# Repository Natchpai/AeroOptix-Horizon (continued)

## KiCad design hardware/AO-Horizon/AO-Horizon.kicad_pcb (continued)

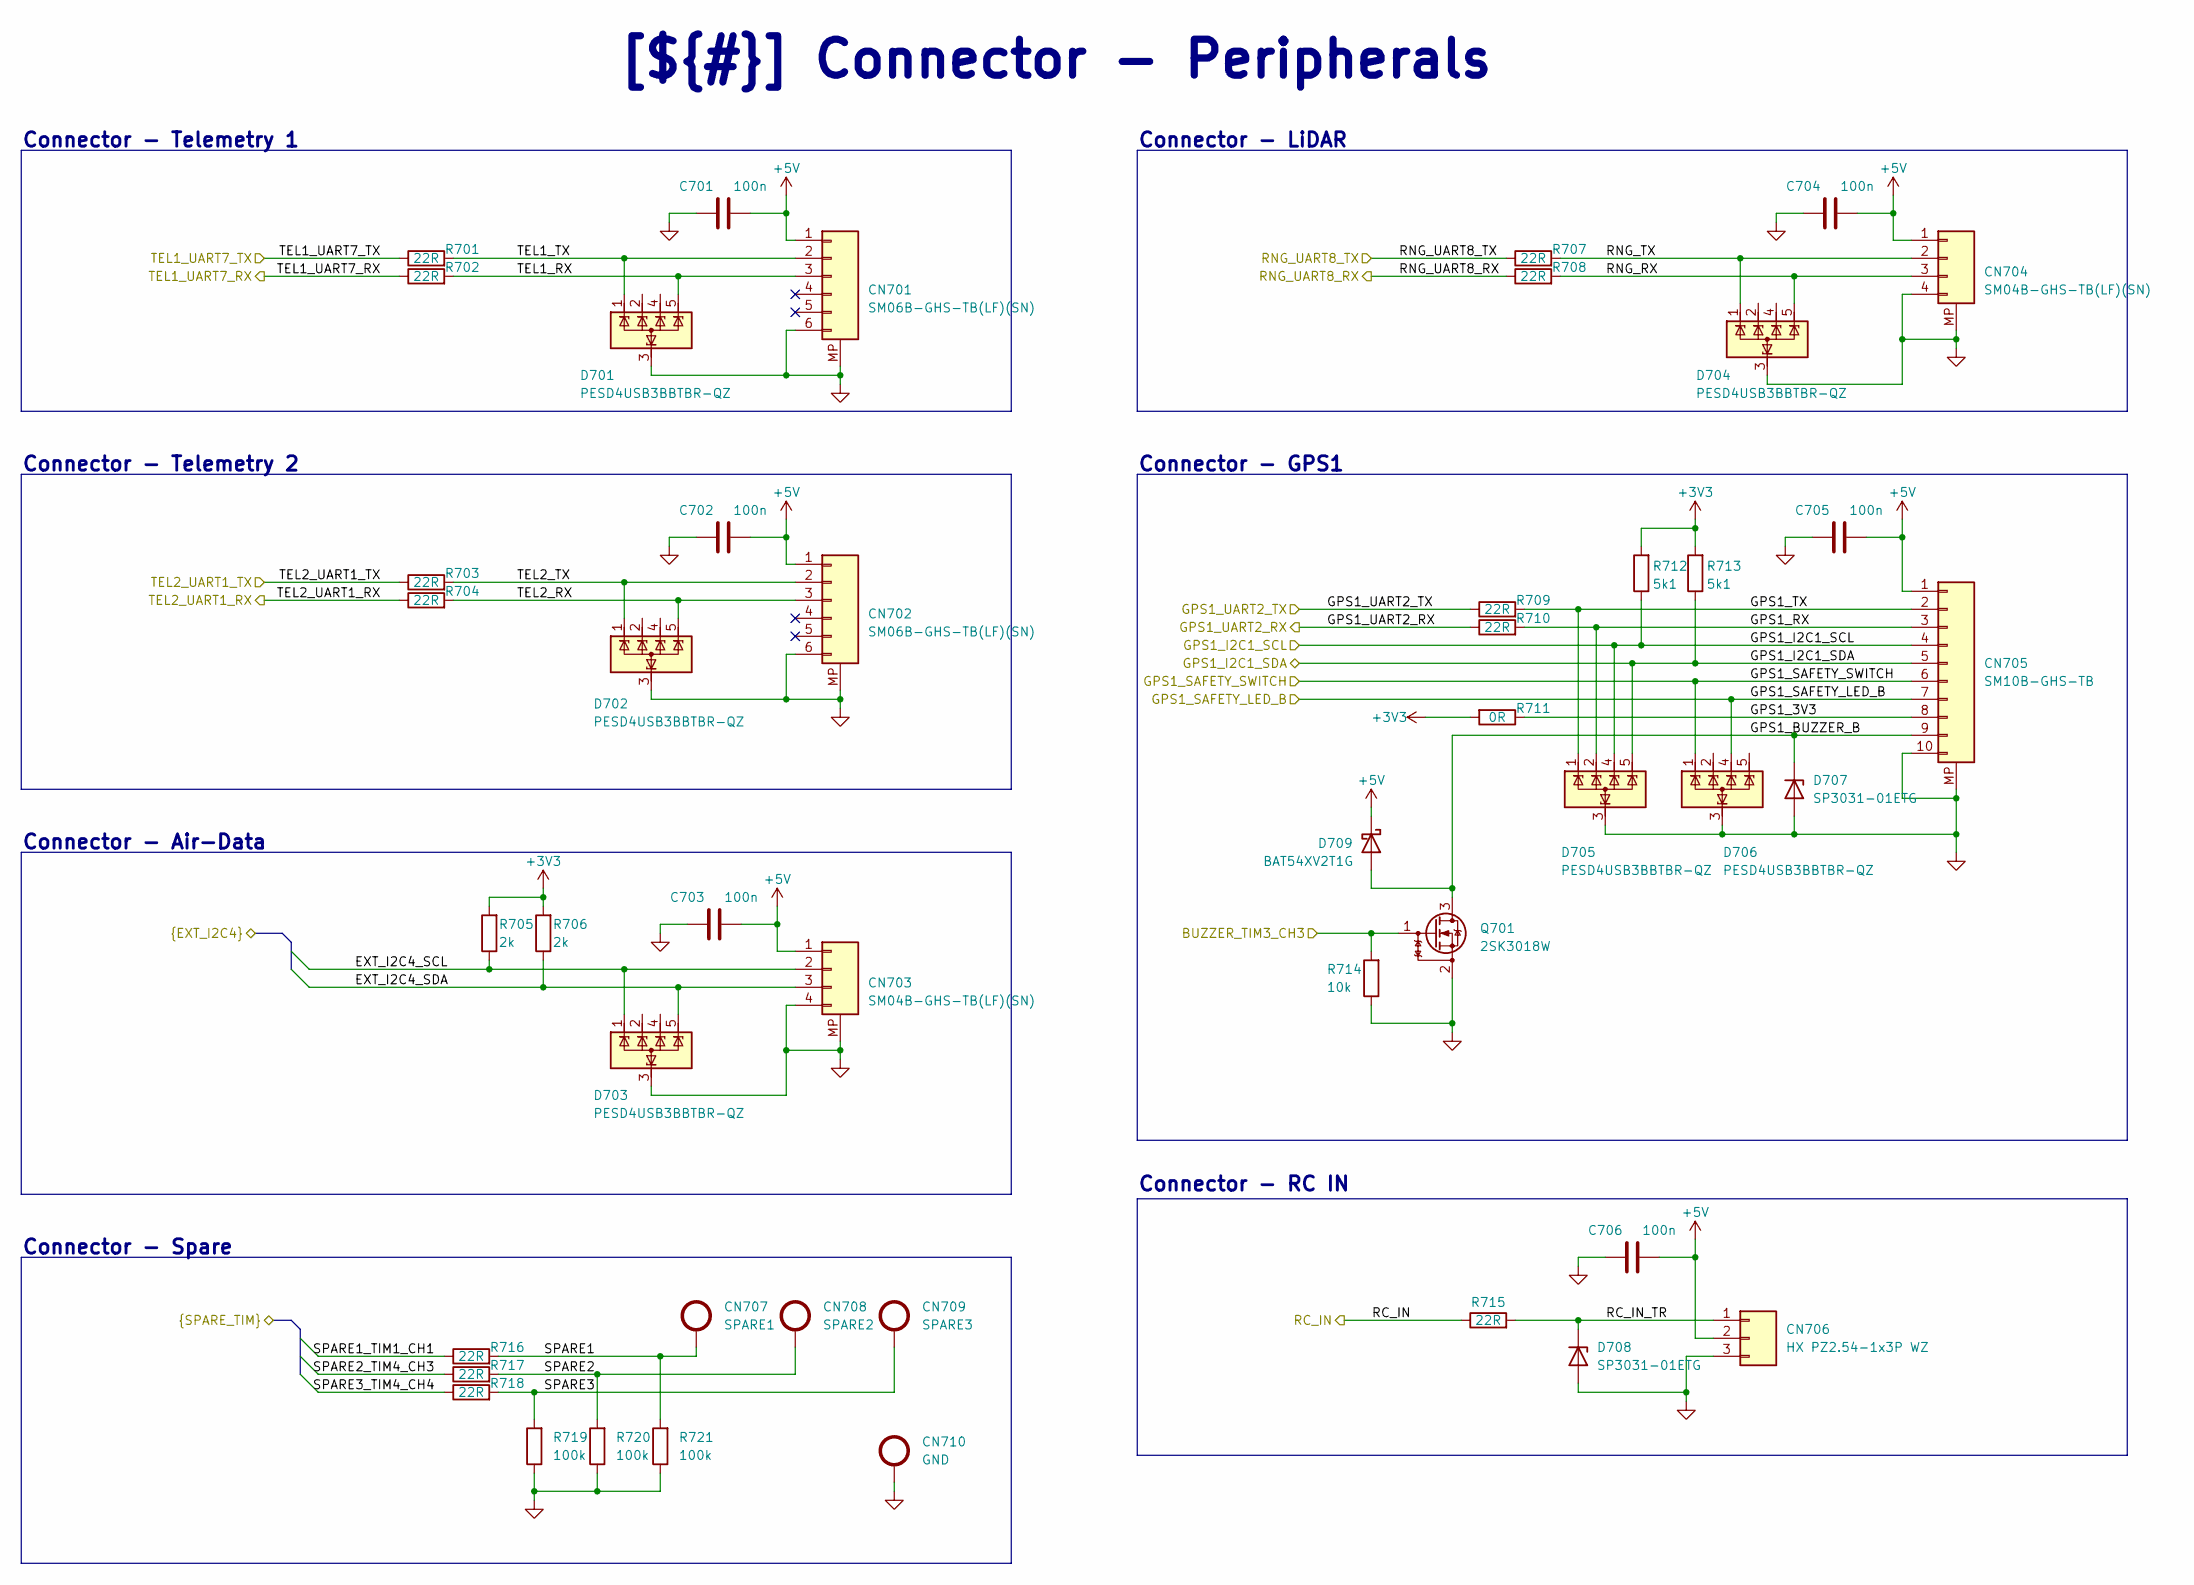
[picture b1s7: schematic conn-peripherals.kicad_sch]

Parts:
C701, C702, C703, C704, C705, C706: 100n; C_0402_1005Metric_NomDensity; MFR.P/N GCM155R71H104KE02D; LCSC C85858
CN701, CN702: SM06B-GHS-TB(LF)(SN); JST_GH_SM06B-GHS-TB_1x06-1MP_P1.25mm_Horizontal; MFR.P/N SM06B-GHS-TB(LF)(SN); LCSC C133065
CN703, CN704: SM04B-GHS-TB(LF)(SN); JST_GH_SM04B-GHS-TB_1x04-1MP_P1.25mm_Horizontal; MFR.P/N SM04B-GHS-TB(LF)(SN); LCSC C189895
CN705: SM10B-GHS-TB; JST_GH_SM10B-GHS-TB_1x10-1MP_P1.25mm_Horizontal; MFR.P/N SM10B-GHS-TB; LCSC C2683602
CN706: HX PZ2.54-1x3P WZ; PinHeader_1x03_P2.54mm_Horizontal; MFR.P/N HX PZ2.54-1x3P WZ; LCSC C32713262
CN707: SPARE1; TestPoint_Pad_D2.0mm
CN708: SPARE2; TestPoint_Pad_D2.0mm
CN709: SPARE3; TestPoint_Pad_D2.0mm
CN710: GND; TestPoint_Pad_D2.0mm
D701, D702, D703, D704, D705, D706: PESD4USB3BBTBR-QZ; Nexperia_SOT1176-2_DFN-10_1x2.5mm_P0.5mm; MFR.P/N PESD4USB3BBTBR-QZ; LCSC C29739485
D707, D708: SP3031-01ETG; D_SOD-882; MFR.P/N SP3031-01ETG; LCSC C207283
D709: BAT54XV2T1G; D_SOD-523; MFR.P/N BAT54XV2T1G; LCSC C81572
Q701: 2SK3018W; SOT-323_SC-70; MFR.P/N 2SK3018W; LCSC C20069149
R701, R702, R703, R704, R707, R708, R709, R710, R715, R716, R717, R718: 22R; R_0402_1005Metric_NomDensity; MFR.P/N RC0402FR-0722RL; LCSC C114765
R705, R706: 2k; R_0402_1005Metric_NomDensity; MFR.P/N RC0402FR-072KL; LCSC C60488
R711: 0R; R_0603_1608Metric_NomDensity; MFR.P/N RC0603FR-070RL; LCSC C100044
R712, R713: 5k1; R_0402_1005Metric_NomDensity; MFR.P/N RC0402FR-075K1L; LCSC C105872
R714: 10k; R_0402_1005Metric_NomDensity; MFR.P/N AC0402FR-0710KL; LCSC C144807
R719, R720, R721: 100k; R_0402_1005Metric_NomDensity; MFR.P/N RC0402FR-07100KL; LCSC C60491

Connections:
+3V3: R705.2, R706.2, R711.2, R712.2, R713.2; also elsewhere on the board
+5V: C701.2, C702.2, C703.2, C704.2, C705.2, C706.2, CN701.1, CN702.1, CN703.1, CN704.1, CN705.1, CN706.2, D709.1 (K); also elsewhere on the board
/Top/Connector - Peripherals/EXT_I2C4_SCL: CN703.2, D703.1 (K), D703.10, R705.1; also elsewhere on the board
/Top/Connector - Peripherals/EXT_I2C4_SDA: CN703.3, D703.5 (K), D703.6, R706.1; also elsewhere on the board
/Top/Connector - Peripherals/GPS1_3V3: CN705.8, R711.1
/Top/Connector - Peripherals/GPS1_BUZZER_B: CN705.9, D707.1, D709.2 (A), Q701.3 (D)
/Top/Connector - Peripherals/GPS1_I2C1_SCL: CN705.4, D705.4 (K), D705.7, R712.1; also elsewhere on the board
/Top/Connector - Peripherals/GPS1_I2C1_SDA: CN705.5, D705.5 (K), D705.6, R713.1; also elsewhere on the board
/Top/Connector - Peripherals/GPS1_RX: CN705.3, D705.2 (K), D705.9, R710.2
/Top/Connector - Peripherals/GPS1_SAFETY_LED_B: CN705.7, D706.4 (K), D706.7; also elsewhere on the board
/Top/Connector - Peripherals/GPS1_SAFETY_SWITCH: CN705.6, D706.1 (K), D706.10; also elsewhere on the board
/Top/Connector - Peripherals/GPS1_TX: CN705.2, D705.1 (K), D705.10, R709.2
/Top/Connector - Peripherals/GPS1_UART2_RX: R710.1; also elsewhere on the board
/Top/Connector - Peripherals/GPS1_UART2_TX: R709.1; also elsewhere on the board
/Top/Connector - Peripherals/RC_IN: R715.1; also elsewhere on the board
/Top/Connector - Peripherals/RC_IN_TR: CN706.1, D708.1, R715.2
/Top/Connector - Peripherals/RNG_RX: CN704.3, D704.5 (K), D704.6, R708.2
/Top/Connector - Peripherals/RNG_TX: CN704.2, D704.1 (K), D704.10, R707.2
/Top/Connector - Peripherals/RNG_UART8_RX: R708.1; also elsewhere on the board
/Top/Connector - Peripherals/RNG_UART8_TX: R707.1; also elsewhere on the board
/Top/Connector - Peripherals/SPARE1: CN707.1 (1_1), R716.2, R721.2
/Top/Connector - Peripherals/SPARE1_TIM1_CH1: R716.1; also elsewhere on the board
/Top/Connector - Peripherals/SPARE2: CN708.1 (1_1), R717.2, R720.2
/Top/Connector - Peripherals/SPARE2_TIM4_CH3: R717.1; also elsewhere on the board
/Top/Connector - Peripherals/SPARE3: CN709.1 (1_1), R718.2, R719.2
/Top/Connector - Peripherals/SPARE3_TIM4_CH4: R718.1; also elsewhere on the board
/Top/Connector - Peripherals/TEL1_RX: CN701.3, D701.5 (K), D701.6, R702.2
/Top/Connector - Peripherals/TEL1_TX: CN701.2, D701.1 (K), D701.10, R701.2
/Top/Connector - Peripherals/TEL1_UART7_RX: R702.1; also elsewhere on the board
/Top/Connector - Peripherals/TEL1_UART7_TX: R701.1; also elsewhere on the board
/Top/Connector - Peripherals/TEL2_RX: CN702.3, D702.5 (K), D702.6, R704.2
/Top/Connector - Peripherals/TEL2_TX: CN702.2, D702.1 (K), D702.10, R703.2
/Top/Connector - Peripherals/TEL2_UART1_RX: R704.1; also elsewhere on the board
/Top/Connector - Peripherals/TEL2_UART1_TX: R703.1; also elsewhere on the board
/Top/MCU - Main FC/BUZZER_TIM3_CH3: Q701.1 (G), R714.2; also elsewhere on the board
GND: C701.1, C702.1, C703.1, C704.1, C705.1, C706.1, CN701.6, CN701.MP (MountPin), CN702.6, CN702.MP (MountPin), CN703.4, CN703.MP (MountPin), CN704.4, CN704.MP (MountPin), CN705.10, CN705.MP (MountPin), CN706.3, CN710.1 (1_1), D701.3 (A), D701.8 (A), D702.3 (A), D702.8 (A), D703.3 (A), D703.8 (A), D704.3 (A), D704.8 (A), D705.3 (A), D705.8 (A), D706.3 (A), D706.8 (A), D707.2, D708.2, Q701.2 (S), R714.1, R719.1, R720.1, R721.1; also elsewhere on the board
unnamed: D701.2 (K), D701.9
unnamed: D701.4 (K), D701.7
unnamed: D702.2 (K), D702.9
unnamed: D702.4 (K), D702.7
unnamed: D703.2 (K), D703.9
unnamed: D703.4 (K), D703.7
unnamed: D704.2 (K), D704.9
unnamed: D704.4 (K), D704.7
unnamed: D706.2 (K), D706.9
unnamed: D706.5 (K), D706.6

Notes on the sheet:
[${#}] ${COMMENT1}
Connector - Air-Data
Connector - GPS1
Connector - Telemetry 2
Connector - RC IN
Connector - Spare
Connector - LiDAR
Connector - Telemetry 1

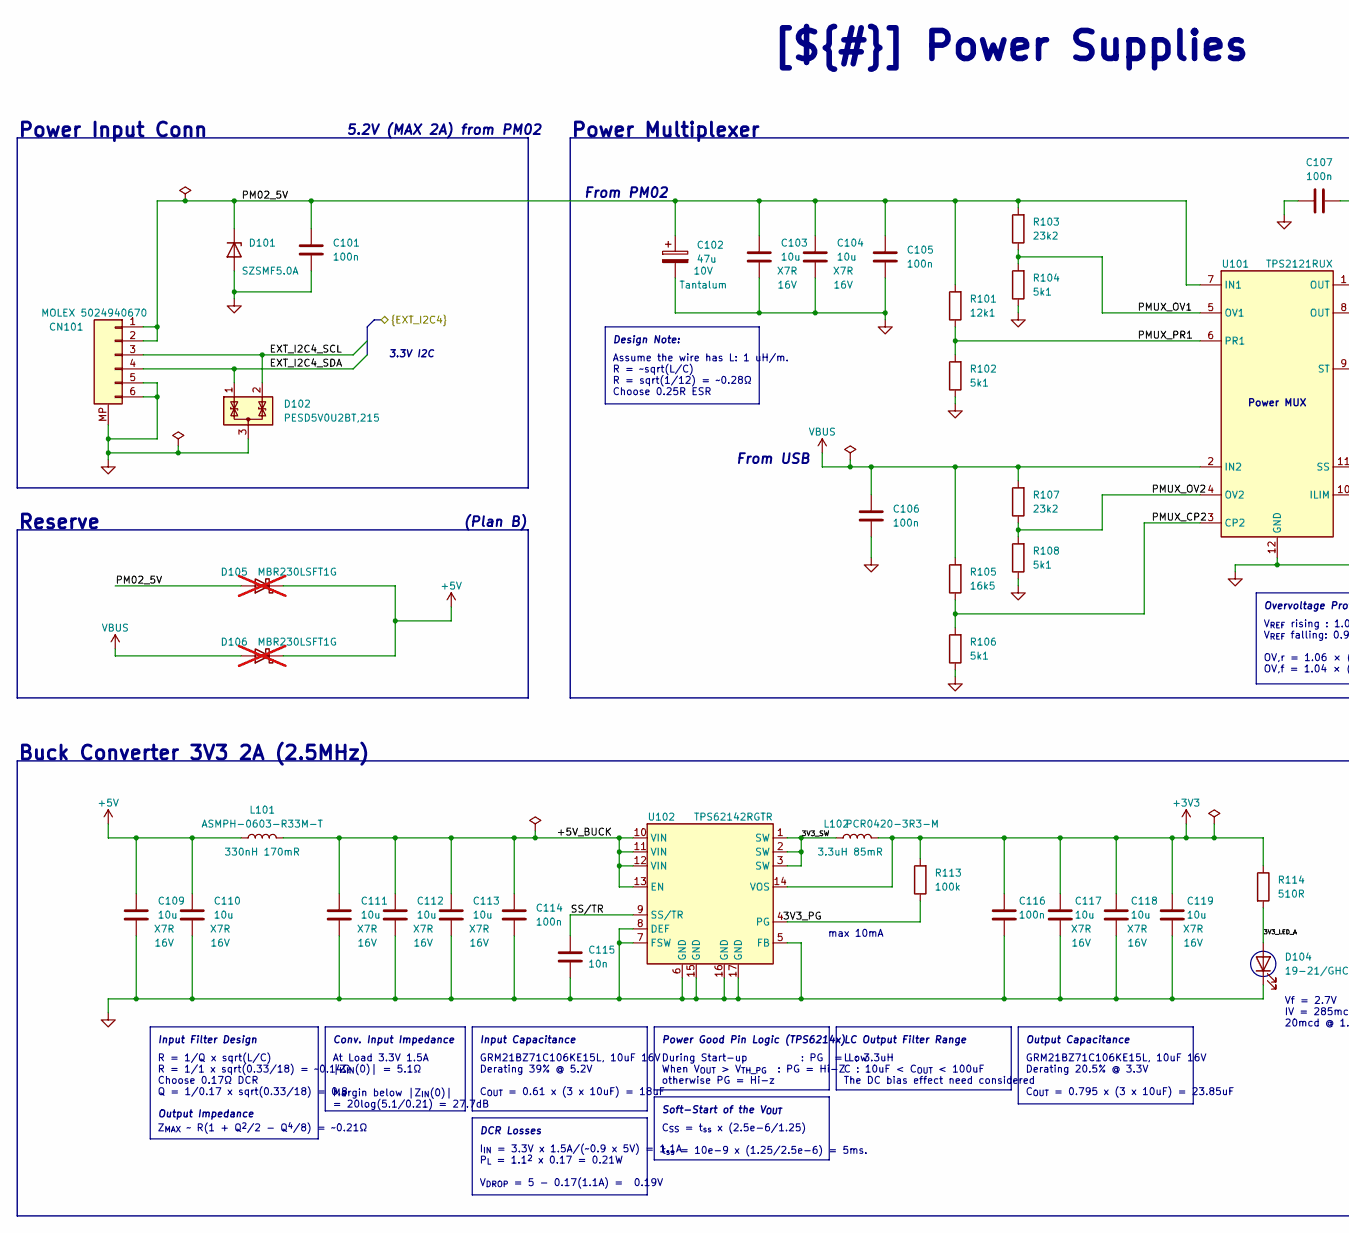
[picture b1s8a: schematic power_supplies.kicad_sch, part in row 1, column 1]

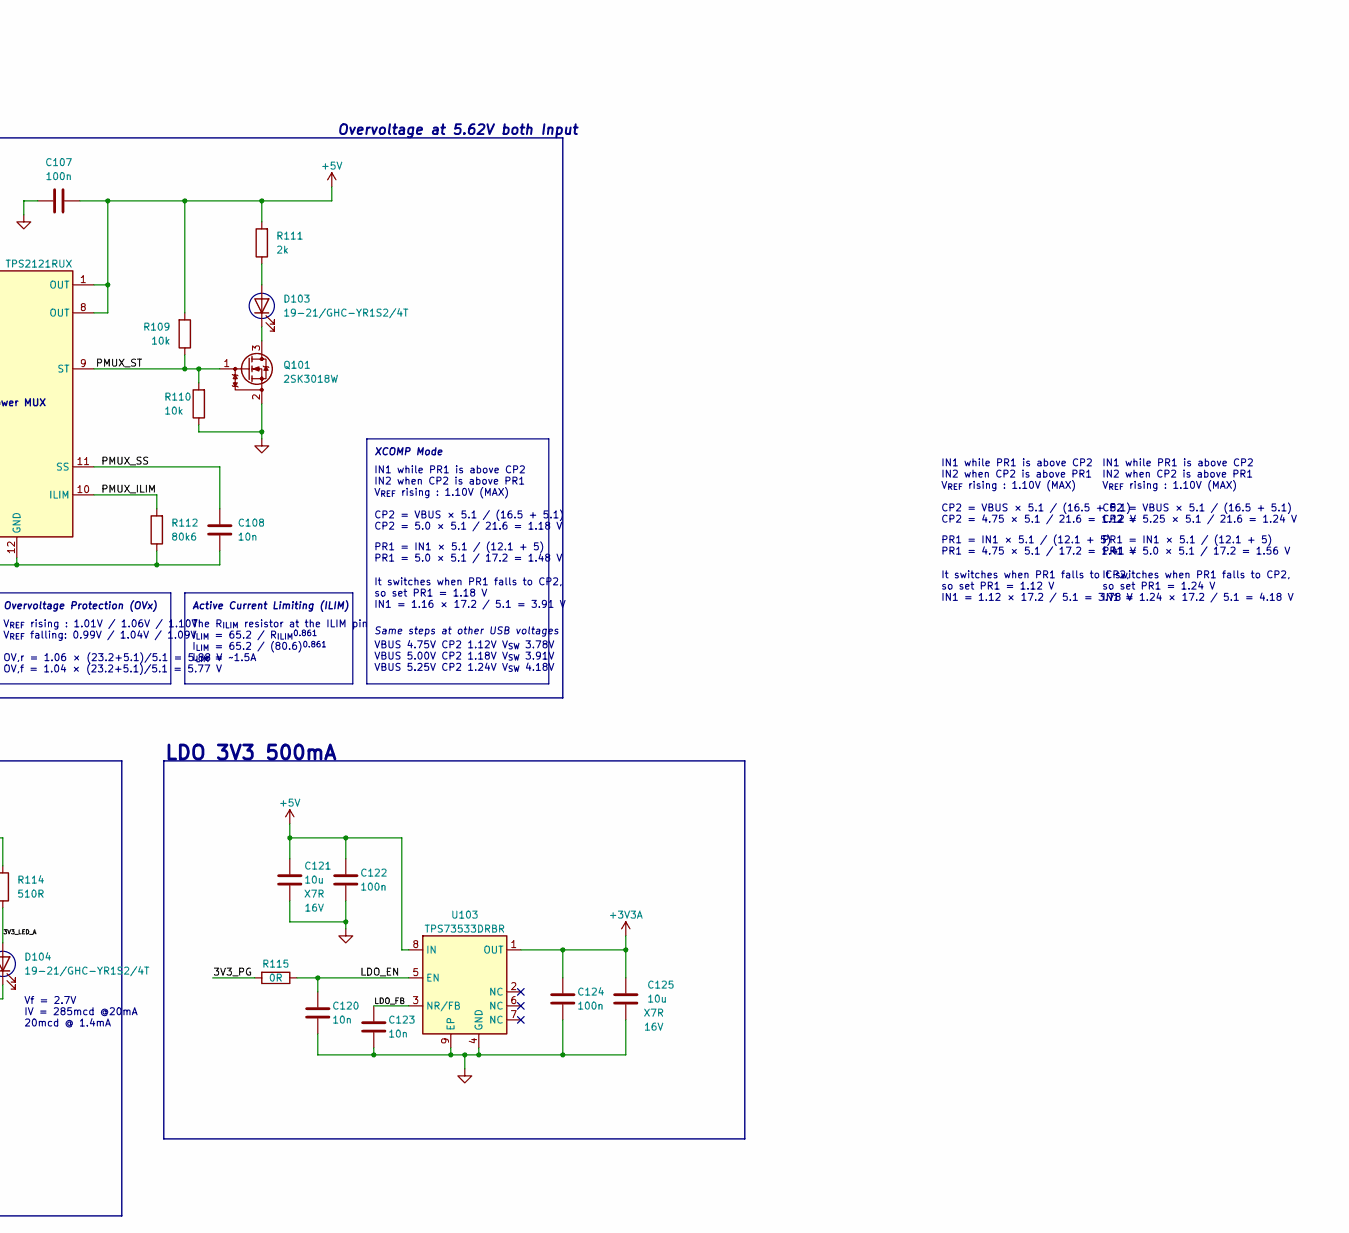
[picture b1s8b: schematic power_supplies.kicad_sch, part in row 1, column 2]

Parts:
C101, C105, C106, C107, C114, C116, C122, C124: 100n; C_0402_1005Metric_NomDensity; MFR.P/N GCM155R71H104KE02D; LCSC C85858
C102: 47u; CP_EIA-3528-21_Kemet-B; MFR.P/N TPSB476K010R0250; LCSC C308881
C103, C104, C109, C110, C111, C112, C113, C117, C118, C119, C121, C125: 10u; C_0805_2012Metric_NomDensity; MFR.P/N GRM21BZ71C106KE15L; LCSC C162430
C108, C115, C120, C123: 10n; C_0402_1005Metric_NomDensity; MFR.P/N GRM1555C1H103JE01D; LCSC C22400107
CN101: MOLEX 5024940670; Molex_CLIK-Mate_502494-0670_1x06-1MP_P2.00mm_Horizontal; MFR.P/N 5024940670; LCSC C587930
D101: SZSMF5.0A; D_SOD-123FL; MFR.P/N SZSMF5.0AT1G; LCSC C5299833
D102: PESD5V0U2BT,215; SOT-23; MFR.P/N PESD5V0U2BT,215; LCSC C85399
D103, D104: 19-21/GHC-YR1S2/4T; LED_0603_1608Metric; MFR.P/N 19-21/GHC-YR1S2/4T; LCSC C2986048
D105, D106: MBR230LSFT1G; D_SOD-123FL; MFR.P/N MBR230LSFT1G; LCSC C126673; not fitted
L101: ASMPH-0603-R33M-T; L_0603_1608Metric; MFR.P/N ASMPH-0603-R33M-T; LCSC C7217516
L102: PCR0420-3R3-M; L_JIERR_PCR0420; MFR.P/N PCR0420-3R3-M; LCSC C53896857
Q101: 2SK3018W; SOT-323_SC-70; MFR.P/N 2SK3018W; LCSC C20069149
R101: 12k1; R_0402_1005Metric_NomDensity; MFR.P/N RC0402FR-0712K1L; LCSC C132157
R102, R104, R106, R108: 5k1; R_0402_1005Metric_NomDensity; MFR.P/N RC0402FR-075K1L; LCSC C105872
R103, R107: 23k2; R_0402_1005Metric_NomDensity; MFR.P/N 0402WGF2322TCE; LCSC C25873
R105: 16k5; R_0402_1005Metric_NomDensity; MFR.P/N RC0402FR-0716K5L; LCSC C276260
R109, R110: 10k; R_0402_1005Metric_NomDensity; MFR.P/N AC0402FR-0710KL; LCSC C144807
R111: 2k; R_0402_1005Metric_NomDensity; MFR.P/N RC0402FR-072KL; LCSC C60488
R112: 80k6; R_0402_1005Metric_NomDensity; MFR.P/N RC0402FR-0780K6L; LCSC C155698
R113: 100k; R_0402_1005Metric_NomDensity; MFR.P/N RC0402FR-07100KL; LCSC C60491
R114: 510R; R_0402_1005Metric_NomDensity; MFR.P/N RC0402FR-07510RL; LCSC C276273
R115: 0R; R_0603_1608Metric_NomDensity; MFR.P/N RC0603FR-070RL; LCSC C100044
U101: TPS2121RUX; Texas_VQFN-HR-12_2x2.5mm_P0.5mm; MFR.P/N TPS2121RUXR; LCSC C485916
U102: TPS62142RGTR; VQFN-16-1EP_3x3mm_P0.5mm_EP1.68x1.68mm_ThermalVias; MFR.P/N TPS62142RGTR; LCSC C129331
U103: TPS73533DRBR; VSON-8-1EP_3x3mm_P0.65mm_EP1.5x1.75mm_ThermalVias; MFR.P/N TPS73533DRBR; LCSC C388480

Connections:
+3V3: C116.1, C117.1, C118.1, C119.1, L102.2, R113.2, R114.1, U102.14 (VOS); also elsewhere on the board
+3V3A: C124.1, C125.1, U103.1 (OUT); also elsewhere on the board
+5V: C107.1, C109.1, C110.1, C121.1, C122.1, D105.1 (K), D106.1 (K), L101.1, R109.2, R111.2, U101.1 (OUT), U101.8 (OUT), U103.8 (IN); also elsewhere on the board
/Top/Connector - Peripherals/EXT_I2C4_SCL: CN101.3, D102.2 (K); also elsewhere on the board
/Top/Connector - Peripherals/EXT_I2C4_SDA: CN101.4, D102.1 (K); also elsewhere on the board
/Top/Power Supplies/3V3_LED_A: D104.2 (A), R114.2
/Top/Power Supplies/3V3_PG: R113.1, R115.2, U102.4 (PG)
/Top/Power Supplies/3V3_SW: L102.1, U102.1 (SW), U102.2 (SW), U102.3 (SW)
/Top/Power Supplies/+5V_BUCK: C111.1, C112.1, C113.1, C114.1, L101.2, U102.10 (VIN), U102.11 (VIN), U102.12 (VIN), U102.13 (EN)
/Top/Power Supplies/LDO_EN: C120.1, R115.1, U103.5 (EN)
/Top/Power Supplies/LDO_FB: C123.1, U103.3 (NR/FB)
/Top/Power Supplies/PM02_5V: C101.1, C102.1, C103.1, C104.1, C105.1, CN101.1, CN101.2, D101.1 (K), D105.2 (A), R101.2, R103.2, U101.7 (IN1)
/Top/Power Supplies/PMUX_CP2: R105.1, R106.2, U101.3 (CP2)
/Top/Power Supplies/PMUX_ILIM: R112.2, U101.10 (ILIM)
/Top/Power Supplies/PMUX_OV1: R103.1, R104.2, U101.5 (OV1)
/Top/Power Supplies/PMUX_OV2: R107.1, R108.2, U101.4 (OV2)
/Top/Power Supplies/PMUX_PR1: R101.1, R102.2, U101.6 (PR1)
/Top/Power Supplies/PMUX_SS: C108.1, U101.11 (SS)
/Top/Power Supplies/PMUX_ST: Q101.1 (G), R109.1, R110.2, U101.9 (ST)
/Top/Power Supplies/SS/TR: C115.1, U102.9 (SS/TR)
GND: C101.2, C102.2, C103.2, C104.2, C105.2, C106.2, C107.2, C108.2, C109.2, C110.2, C111.2, C112.2, C113.2, C114.2, C115.2, C116.2, C117.2, C118.2, C119.2, C120.2, C121.2, C122.2, C123.2, C124.2, C125.2, CN101.5, CN101.6, CN101.MP (MountPin), D101.2 (A), D102.3 (A), D104.1 (K), Q101.2 (S), R102.1, R104.1, R106.1, R108.1, R110.1, R112.1, U101.12 (GND), U102.5 (FB), U102.6 (GND), U102.7 (FSW), U102.8 (DEF), U102.15 (GND), U102.16 (GND), U102.17 (GND), U103.4 (GND), U103.9 (EP); also elsewhere on the board
unnamed: D103.2 (A), R111.1
unnamed: D103.1 (K), Q101.3 (D)
VBUS: C106.1, D106.2 (A), R105.2, R107.2, U101.2 (IN2); also elsewhere on the board

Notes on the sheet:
DCR Losses
Margin below |Z_{IN}(0)| = 20log(5.1/0.21) = 27.7dB
max 10mA
Soft-Start of the V_{OUT}
PR1 = IN1 × 5.1 / (12.1 + 5) PR1 = 4.75 × 5.1 / 17.2 = 1.41 V
V_{REF} rising : 1.01V / 1.06V / 1.10V V_{REF} falling: 0.99V / 1.04V / 1.09V OV,r = 1.06 × (23.2+5.1)/5.1 = 5.88 V OV,f = 1.04 × (23.2+5.1)/5.1 = 5.77 V
IN1 while PR1 is above CP2 IN2 when CP2 is above PR1 V_{REF} rising : 1.10V (MAX) CP2 = VBUS × 5.1 / (16.5 + 5.1) CP2 = 5.0 × 5.1 / 21.6 = 1.18 V
From PM02
(Plan B)
I_{IN} = 3.3V x 1.5A/(~0.9 x 5V) = 1.1A P_{L} = 1.1^{2} x 0.17 = 0.21W V_{DROP} = 5 - 0.17(1.1A) = 0.19V
Assume the wire has L: 1 uH/m. R = ~sqrt(L/C) R = sqrt(1/12) = ~0.28Ω Choose 0.25R ESR
Conv. Input Impedance
Input Filter Design
Power Good Pin Logic (TPS6214x)
L : 3.3uH C : 10uF < C_{OUT} < 100uF The DC bias effect need considered
3.3V I2C
Input Capacitance
Output Impedance
During Start-up : PG = Low When V_{OUT} > V_{TH_PG} : PG = Hi-Z otherwise PG = Hi-z
It switches when PR1 falls to CP2, so set PR1 = 1.24 V IN1 = 1.24 × 17.2 / 5.1 = 4.18 V
PR1 = IN1 × 5.1 / (12.1 + 5) PR1 = 5.0 × 5.1 / 17.2 = 1.56 V
C_{SS} = t_{ss} x (2.5e-6/1.25) t_{ss} = 10e-9 x (1.25/2.5e-6) = 5ms.
GRM21BZ71C106KE15L, 10uF 16V Derating 39% @ 5.2V C_{OUT} = 0.61 x (3 x 10uF) = 18uF
Same steps at other USB voltages
LDO 3V3 500mA
XCOMP Mode
Vf = 2.7V IV = 285mcd @20mA 20mcd @ 1.4mA
Power Input Conn
It switches when PR1 falls to CP2, so set PR1 = 1.18 V IN1 = 1.16 × 17.2 / 5.1 = 3.91 V
IN1 while PR1 is above CP2 IN2 when CP2 is above PR1 V_{REF} rising : 1.10V (MAX) CP2 = VBUS × 5.1 / (16.5 + 5.1) CP2 = 5.25 × 5.1 / 21.6 = 1.24 V
The R_{ILIM} resistor at the ILIM pin I_{LIM} = 65.2 / R_{ILIM}^{0.861} I_{LIM} = 65.2 / (80.6)^{0.861} I_{LIM} = ~1.5A
Overvoltage Protection (OVx)
LC Output Filter Range
Power Multiplexer
Power MUX
From USB
Overvoltage at 5.62V both Input
Output Capacitance
VBUS 4.75V CP2 1.12V V_{SW} 3.78V VBUS 5.00V CP2 1.18V V_{SW} 3.91V VBUS 5.25V CP2 1.24V V_{SW} 4.18V
Z_{MAX} ~ R(1 + Q^{2}/2 - Q^{4}/8) = ~0.21Ω

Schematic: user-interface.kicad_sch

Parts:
B901, B902: PTS815SJM250SMTRLFS; SW_Push_SPST_NO_CK_PTS815_4.2x3.2mm_H2.5mm; MFR.P/N PTS815SJM250SMTRLFS; LCSC C2689510
D901, D902: AAA3528LSEEZGKQBKS; LED_SMD_2835_Kingbright_AAA3528LSEEZGKQBKS; MFR.P/N AAA3528LSEEZGKQBKS; LCSC C5547384
H901, H902, H903, H904: MountingHole_Pad; MountingHole_3.2mm_M3_Pad_Via
R901, R902, R903, R904, R905, R906: 220R; R_0402_1005Metric_NomDensity; MFR.P/N RC0402FR-07220RL; LCSC C112291

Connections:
+3V3: B902.1, B902.2, D901.2 (A), D902.2 (A); also elsewhere on the board
/Top/Connector - USB & Debug/RESET_B: B901.1, B901.2; also elsewhere on the board
/Top/MCU - IO/LED_IO_BLUE_B: R906.2; also elsewhere on the board
/Top/MCU - IO/LED_IO_GREEN_B: R905.2; also elsewhere on the board
/Top/MCU - IO/LED_IO_RED_B: R904.2; also elsewhere on the board
/Top/MCU - Main FC/H7_BOOT0: B902.3, B902.4; also elsewhere on the board
/Top/MCU - Main FC/LED_MAIN_BLUE_B: R903.2; also elsewhere on the board
/Top/MCU - Main FC/LED_MAIN_GREEN_B: R902.2; also elsewhere on the board
/Top/MCU - Main FC/LED_MAIN_RED_B: R901.2; also elsewhere on the board
/Top/User - Interface/LED_IO_B_K: D902.4 (BK), R906.1
/Top/User - Interface/LED_IO_G_K: D902.3 (GK), R905.1
/Top/User - Interface/LED_IO_R_K: D902.1 (RK), R904.1
/Top/User - Interface/LED_MAIN_B_K: D901.4 (BK), R903.1
/Top/User - Interface/LED_MAIN_G_K: D901.3 (GK), R902.1
/Top/User - Interface/LED_MAIN_R_K: D901.1 (RK), R901.1
GND: B901.3, B901.4; also elsewhere on the board

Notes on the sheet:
BOARD_ARMED_STATE_LED
STAT
[${#}] ${COMMENT1}
LED_GREEN
IO SAFE
BOOT0 Button
Status LEDs
IO TEST
Miscellaneous
ERR
TBD(Software)
ARM
LED_BLUE
LED_AMBER
BOARD_OVERLOAD_LED
Reset Button

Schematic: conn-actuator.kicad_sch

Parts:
C801, C802: 68u; CP_EIA-6032-28_Kemet-C; MFR.P/N T495C686M016ATE250; LCSC C122319
C803, C804, C805, C806: 22u; C_1210_3225Metric_NomDensity; MFR.P/N GRM32ER71E226KE15L; LCSC C21397
C807, C808: 100n; C_0402_1005Metric_NomDensity; MFR.P/N GCM155R71H104KE02D; LCSC C85858
CN801, CN802, CN803: TSW-104-08-F-T-RA; SAMTEC_TSW-104-08-F-T-RA; MFR.P/N TSW-104-08-F-T-RA; LCSC C5803971
CN804, CN805: TSW-101-22-G-T-RA; SAMTEC_TSW-101-22-G-T-RA; MFR.P/N TSW-101-22-G-T-RA; LCSC C6292018
D801, D802, D803, D804, D805, D806: PESD5V0U2BT,215; SOT-23; MFR.P/N PESD5V0U2BT,215; LCSC C85399
D807, D808: SMF8.5A; D_SOD-123FL; MFR.P/N SMF8.5A; LCSC C50325386
R801, R802, R803, R804, R809, R810, R811, R812, R817, R818, R819, R820: 22R; R_0402_1005Metric_NomDensity; MFR.P/N RC0402FR-0722RL; LCSC C114765
R805, R806, R807, R808, R813, R814, R815, R816, R821, R822, R823, R824: 100k; R_0402_1005Metric_NomDensity; MFR.P/N RC0402FR-07100KL; LCSC C60491
R825, R827: 46k4; R_0402_1005Metric_NomDensity; MFR.P/N RT0402FRE0746K4L; LCSC C854332
R826, R828: 23k2; R_0402_1005Metric_NomDensity; MFR.P/N 0402WGF2322TCE; LCSC C25873

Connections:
/Top/Connector - Actuator/+VSERVO1: C801.1, C803.1, C804.1, CN801.1b, CN801.2b, CN801.3b, CN801.4b, CN804.1b, D807.1 (K), R825.2
/Top/Connector - Actuator/+VSERVO2: C802.1, C805.1, C806.1, CN803.1b, CN803.2b, CN803.3b, CN803.4b, CN805.1b, D808.1 (K), R827.2
/Top/Connector - Actuator/AUX1: CN801.1c, D801.1 (K), R801.2, R808.2
/Top/Connector - Actuator/AUX1_TIM5_CH1: R801.1; also elsewhere on the board
/Top/Connector - Actuator/AUX2: CN801.2c, D801.2 (K), R802.2, R807.2
/Top/Connector - Actuator/AUX2_TIM5_CH2: R802.1; also elsewhere on the board
/Top/Connector - Actuator/AUX3: CN801.3c, D802.1 (K), R803.2, R806.2
/Top/Connector - Actuator/AUX3_TIM5_CH3: R803.1; also elsewhere on the board
/Top/Connector - Actuator/AUX4: CN801.4c, D802.2 (K), R804.2, R805.2
/Top/Connector - Actuator/AUX4_TIM5_CH4: R804.1; also elsewhere on the board
/Top/Connector - Actuator/MAIN1: CN802.1c, D803.1 (K), R809.2, R816.2
/Top/Connector - Actuator/MAIN1_TIM2_CH1: R809.1; also elsewhere on the board
/Top/Connector - Actuator/MAIN2: CN802.2c, D803.2 (K), R810.2, R815.2
/Top/Connector - Actuator/MAIN2_TIM2_CH2: R810.1; also elsewhere on the board
/Top/Connector - Actuator/MAIN3: CN802.3c, D804.1 (K), R811.2, R814.2
/Top/Connector - Actuator/MAIN3_TIM4_CH3: R811.1; also elsewhere on the board
/Top/Connector - Actuator/MAIN4: CN802.4c, D804.2 (K), R812.2, R813.2
/Top/Connector - Actuator/MAIN4_TIM4_CH4: R812.1; also elsewhere on the board
/Top/Connector - Actuator/MAIN5: CN803.1c, D805.1 (K), R817.2, R824.2
/Top/Connector - Actuator/MAIN5_TIM3_CH1: R817.1; also elsewhere on the board
/Top/Connector - Actuator/MAIN6: CN803.2c, D805.2 (K), R818.2, R823.2
/Top/Connector - Actuator/MAIN6_TIM3_CH2: R818.1; also elsewhere on the board
/Top/Connector - Actuator/MAIN7: CN803.3c, D806.1 (K), R819.2, R822.2
/Top/Connector - Actuator/MAIN7_TIM3_CH3: R819.1; also elsewhere on the board
/Top/Connector - Actuator/MAIN8: CN803.4c, D806.2 (K), R820.2, R821.2
/Top/Connector - Actuator/MAIN8_TIM3_CH4: R820.1; also elsewhere on the board
/Top/Connector - Actuator/SERVO_V_ADC1_IN4: C807.1, R825.1, R826.2; also elsewhere on the board
/Top/Connector - Actuator/SERVO_V_ADC1_IN5: C808.1, R827.1, R828.2; also elsewhere on the board
GND: C801.2, C802.2, C803.2, C804.2, C805.2, C806.2, C807.2, C808.2, CN801.1a, CN801.2a, CN801.3a, CN801.4a, CN802.1a, CN802.2a, CN802.3a, CN802.4a, CN803.1a, CN803.2a, CN803.3a, CN803.4a, CN804.1a, CN805.1a, D801.3 (A), D802.3 (A), D803.3 (A), D804.3 (A), D805.3 (A), D806.3 (A), D807.2 (A), D808.2 (A), R805.1, R806.1, R807.1, R808.1, R813.1, R814.1, R815.1, R816.1, R821.1, R822.1, R823.1, R824.1, R826.1, R828.1; also elsewhere on the board

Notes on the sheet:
[${#}] ${COMMENT1}
3:1
Connector - Servo Rail Input
Pull-down TR Resistor
Servo Rail Sense
Connector - Surface Servo
8.4V MAX
Connector - Tilt Servo
Connector - ESC

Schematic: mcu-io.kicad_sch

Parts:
C301: 4u7; C_0603_1608Metric_NomDensity; MFR.P/N GRM188Z71C475KE21D; LCSC C389010
C302, C303, C304, C305, C306, C308, C309, C312: 100n; C_0402_1005Metric_NomDensity; MFR.P/N GCM155R71H104KE02D; LCSC C85858
C307: 2u2; C_0603_1608Metric_NomDensity; MFR.P/N GRM188Z71C225KE43D; LCSC C576485
C310, C311: 10n; C_0402_1005Metric_NomDensity; MFR.P/N GRM1555C1H103JE01D; LCSC C22400107
D301: BAT54XV2T1G; D_SOD-523; MFR.P/N BAT54XV2T1G; LCSC C81572
R301, R302, R303, R304, R305, R306, R314: 22R; R_0402_1005Metric_NomDensity; MFR.P/N RC0402FR-0722RL; LCSC C114765
R307, R308, R309, R310, R312: 10k; R_0402_1005Metric_NomDensity; MFR.P/N AC0402FR-0710KL; LCSC C144807
R311: 10k; R_0402_1005Metric_NomDensity; MFR.P/N AC0402FR-0710KL; LCSC C144807; not fitted
R313: 100k; R_0402_1005Metric_NomDensity; MFR.P/N RC0402FR-07100KL; LCSC C60491
U301: STM32F100C8T6B; LQFP-48_7x7mm_P0.5mm; MFR.P/N STM32F100C8T6B; LCSC C8288
U302: ASDDV-24.000MHZ-LC-T; Oscillator_SMD_Abracon_ASDDV-4Pin_2.5x2.0mm; MFR.P/N ASDDV-24.000MHZ-LC-T; LCSC C17195695
U303: SN74LVC1G34DCKR; Texas_DCK0005A_SC-70-5_2x1.25mm_P0.65mm; MFR.P/N SN74LVC1G34DCKR; LCSC C353880

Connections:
+3V3: C301.1, C302.1, C303.1, C304.1, C305.1, C309.1, C312.2, R301.1, R307.1, R310.2, R311.2, U301.1 (VBAT), U301.24 (VDD), U301.36 (VDD), U301.48 (VDD), U302.1 (EN), U302.4 (VDD), U303.5 (VCC); also elsewhere on the board
/Top/Connector - Actuator/MAIN1_TIM2_CH1: U301.10 (PA0); also elsewhere on the board
/Top/Connector - Actuator/MAIN2_TIM2_CH2: U301.11 (PA1); also elsewhere on the board
/Top/Connector - Actuator/MAIN3_TIM4_CH3: U301.45 (PB8); also elsewhere on the board
/Top/Connector - Actuator/MAIN4_TIM4_CH4: U301.46 (PB9); also elsewhere on the board
/Top/Connector - Actuator/MAIN5_TIM3_CH1: U301.16 (PA6); also elsewhere on the board
/Top/Connector - Actuator/MAIN6_TIM3_CH2: U301.17 (PA7); also elsewhere on the board
/Top/Connector - Actuator/MAIN7_TIM3_CH3: U301.18 (PB0); also elsewhere on the board
/Top/Connector - Actuator/MAIN8_TIM3_CH4: U301.19 (PB1); also elsewhere on the board
/Top/Connector - Actuator/SERVO_V_ADC1_IN4: R305.2; also elsewhere on the board
/Top/Connector - Actuator/SERVO_V_ADC1_IN5: R306.2; also elsewhere on the board
/Top/Connector - Peripherals/GPS1_SAFETY_LED_B: U301.26 (PB13); also elsewhere on the board
/Top/Connector - Peripherals/GPS1_SAFETY_SWITCH: R309.2, U301.41 (PB5); also elsewhere on the board
/Top/Connector - Peripherals/RC_IN: R313.2, U303.2 (IN); also elsewhere on the board
/Top/Connector - USB & Debug/DBG_UART1_TX: U301.30 (PA9); also elsewhere on the board
/Top/Connector - USB & Debug/F1_SWCLK: U301.37 (PA14); also elsewhere on the board
/Top/Connector - USB & Debug/F1_SWDIO: U301.34 (PA13); also elsewhere on the board
/Top/Connector - USB & Debug/RESET_B: D301.1 (K); also elsewhere on the board
/Top/MCU - IO/F1_ADC1_IN4: C310.1, R305.1, U301.14 (PA4)
/Top/MCU - IO/F1_ADC1_IN5: C311.1, R306.1, U301.15 (PA5)
/Top/MCU - IO/F1_BOOT0: R311.1, R312.2, U301.44 (BOOT0)
/Top/MCU - IO/F1_BOOT1: U301.20 (PB2)
/Top/MCU - IO/F1_CLK_24M00: R302.2, U301.5 (PD0)
/Top/MCU - IO/F1_PA10: R307.2, U301.31 (PA10)
/Top/MCU - IO/F1_PA12: R308.2, U301.33 (PA12)
/Top/MCU - IO/F1_PA15: U301.38 (PA15)
/Top/MCU - IO/F1_PB3: U301.39 (PB3)
/Top/MCU - IO/F1_PB4: U301.40 (PB4)
/Top/MCU - IO/F1_PB6: U301.42 (PB6)
/Top/MCU - IO/F1_PB7: U301.43 (PB7)
/Top/MCU - IO/F1_PB10: U301.21 (PB10)
/Top/MCU - IO/F1_PB11: R310.1, U301.22 (PB11)
/Top/MCU - IO/F1_PB12: U301.25 (PB12)
/Top/MCU - IO/F1_PC13: U301.2 (PC13)
/Top/MCU - IO/F1_PC14: U301.3 (PC14)
/Top/MCU - IO/F1_PC15: U301.4 (PC15)
/Top/MCU - IO/F1_PD1: U301.6 (PD1)
/Top/MCU - IO/F1_RESET_B: C308.1, D301.2 (A), U301.7 (NRST)
/Top/MCU - IO/F1_UART2_RX: R304.1, U301.13 (PA3)
/Top/MCU - IO/F1_UART2_TX: R303.1, U301.12 (PA2)
/Top/MCU - IO/F1_VDDA: C306.1, C307.1, R301.2, U301.9 (VDDA)
/Top/MCU - IO/LED_IO_BLUE_B: U301.27 (PB14); also elsewhere on the board
/Top/MCU - IO/LED_IO_GREEN_B: U301.32 (PA11); also elsewhere on the board
/Top/MCU - IO/LED_IO_RED_B: U301.28 (PB15); also elsewhere on the board
/Top/MCU - IO/OSC_24M00_OUT: R302.1, U302.3 (OUT)
/Top/MCU - IO/RCIN_TIM1_CH1: R314.1, U301.29 (PA8)
/Top/MCU - IO/RC_IN_BUFFER: R314.2, U303.4 (OUT)
/Top/MCU - Main FC/H7_UART6_RX: R303.2; also elsewhere on the board
/Top/MCU - Main FC/H7_UART6_TX: R304.2; also elsewhere on the board
GND: C301.2, C302.2, C303.2, C304.2, C305.2, C306.2, C307.2, C308.2, C309.2, C310.2, C311.2, C312.1, R308.1, R309.1, R312.1, R313.1, U301.8 (VSSA), U301.23 (VSS), U301.35 (VSS), U301.47 (VSS), U302.2 (GND), U303.3 (GND); also elsewhere on the board

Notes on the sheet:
Conn - GPS1
BOOT Mode
Conn - Surface Servo
F1-Debug
Conn - RC IN
Conn - ESC
RC IN Buffer
[${#}] ${COMMENT1}
User - Interface

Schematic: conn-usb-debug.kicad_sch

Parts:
C601, C602, C603: 100n; C_0402_1005Metric_NomDensity; MFR.P/N GCM155R71H104KE02D; LCSC C85858
CN601: USB4105-GF-A; USB_C_Receptacle_GCT_USB4105-xx-A_16P_TopMnt_Horizontal; MFR.P/N USB4105-GF-A; LCSC C3020560
CN602: SM06B-SRSS-TB(LF)(SN); JST_SH_SM06B-SRSS-TB_1x06-1MP_P1.00mm_Horizontal; MFR.P/N SM06B-SRSS-TB(LF)(SN); LCSC C160405
R601, R602, R603: 5k1; R_0402_1005Metric_NomDensity; MFR.P/N RC0402FR-075K1L; LCSC C105872
R604: 10k; R_0402_1005Metric_NomDensity; MFR.P/N AC0402FR-0710KL; LCSC C144807
R605, R606, R607, R608, R609, R610, R611, R612, R613: 22R; R_0402_1005Metric_NomDensity; MFR.P/N RC0402FR-0722RL; LCSC C114765
TP601: F1_VREF33; TestPoint_Pad_D2.0mm
TP602: F1_TX; TestPoint_Pad_D2.0mm
TP603: F1_SWDIO; TestPoint_Pad_D2.0mm
TP604: F1_SWCLK; TestPoint_Pad_D2.0mm
TP605: RESET_B; TestPoint_Pad_D2.0mm
TP606: GND; TestPoint_Pad_D2.0mm
U601: USBLC6-2SC6; SOT-23-6; MFR.P/N USBLC6-2SC6; LCSC C7519

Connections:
+3V3: R609.2, R613.2; also elsewhere on the board
/Top/Connector - USB & Debug/DBG_F1_SWCLK: R612.1, TP604.1 (1_1)
/Top/Connector - USB & Debug/DBG_F1_SWDIO: R611.1, TP603.1 (1_1)
/Top/Connector - USB & Debug/DBG_F1_TX: R610.1, TP602.1 (1_1)
/Top/Connector - USB & Debug/DBG_H7_RX: CN602.3, R606.1
/Top/Connector - USB & Debug/DBG_H7_SWCLK: CN602.5, R608.1
/Top/Connector - USB & Debug/DBG_H7_SWDIO: CN602.4, R607.1
/Top/Connector - USB & Debug/DBG_H7_TX: CN602.2, R605.1
/Top/Connector - USB & Debug/DBG_UART1_TX: R610.2; also elsewhere on the board
/Top/Connector - USB & Debug/DBG_UART3_RX: R606.2; also elsewhere on the board
/Top/Connector - USB & Debug/DBG_UART3_TX: R605.2; also elsewhere on the board
/Top/Connector - USB & Debug/F1_SWCLK: R612.2; also elsewhere on the board
/Top/Connector - USB & Debug/F1_SWDIO: R611.2; also elsewhere on the board
/Top/Connector - USB & Debug/F1_TARGET_VREF33: C603.1, R613.1, TP601.1 (1_1)
/Top/Connector - USB & Debug/H7_SWCLK: R608.2; also elsewhere on the board
/Top/Connector - USB & Debug/H7_SWDIO: R607.2; also elsewhere on the board
/Top/Connector - USB & Debug/H7_TARGET_VREF33: C602.1, CN602.1, R609.1
/Top/Connector - USB & Debug/RESET_B: TP605.1 (1_1); also elsewhere on the board
/Top/Connector - USB & Debug/USB_CC1: CN601.A5 (CC1), R602.2
/Top/Connector - USB & Debug/USB_CC2: CN601.B5 (CC2), R601.2
/Top/Connector - USB & Debug/USB_D_N: CN601.A7 (D-), CN601.B7 (D-), U601.1 (I/O1)
/Top/Connector - USB & Debug/USB_D_P: CN601.A6 (D+), CN601.B6 (D+), U601.3 (I/O2)
/Top/Connector - USB & Debug/USB_FS_D_N: U601.6 (I/O1); also elsewhere on the board
/Top/Connector - USB & Debug/USB_FS_D_P: U601.4 (I/O2); also elsewhere on the board
/Top/Connector - USB & Debug/USB_FS_VBUS: R603.1, R604.2; also elsewhere on the board
GND: C601.2, C602.2, C603.2, CN601.A1 (GND), CN601.A12 (GND), CN601.B1 (GND), CN601.B12 (GND), CN601.SH (SHIELD), CN602.6, CN602.MP (MountPin), R601.1, R602.1, R604.1, TP606.1 (1_1), U601.2 (GND); also elsewhere on the board
VBUS: C601.1, CN601.A4 (VBUS), CN601.A9 (VBUS), CN601.B4 (VBUS), CN601.B9 (VBUS), R603.2, U601.5 (VBUS); also elsewhere on the board

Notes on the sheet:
SWD-F1 Connector
SWD-H7 Connector
USB-C Connector
[${#}] ${COMMENT1}

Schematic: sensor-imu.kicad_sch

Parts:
C401, C402, C403, C404: 100n; C_0402_1005Metric_NomDensity; MFR.P/N GCM155R71H104KE02D; LCSC C85858
U401, U402: ICM-45686; Bosch_LGA-14_3x2.5mm_P0.5mm; MFR.P/N ICM-45686; LCSC C22459454

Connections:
+3V3: C401.1, C403.1, U401.5 (VDDIO), U402.5 (VDDIO); also elsewhere on the board
+3V3A: C402.1, C404.1, U401.8 (VDD), U402.8 (VDD); also elsewhere on the board
/Top/MCU - Main FC/IMU1_INT1: U401.4 (INT1); also elsewhere on the board
/Top/MCU - Main FC/IMU1_SPI1_CLK: U401.13 (AP_SCL/AP_SCLK); also elsewhere on the board
/Top/MCU - Main FC/IMU1_SPI1_CS: U401.12 (AP_CS); also elsewhere on the board
/Top/MCU - Main FC/IMU1_SPI1_SDI: U401.14 (AP_SDA/AP_SDIO/AP_SDI); also elsewhere on the board
/Top/MCU - Main FC/IMU1_SPI1_SDO: U401.1 (AP_SDO/AP_AD0); also elsewhere on the board
/Top/MCU - Main FC/IMU2_INT1: U402.4 (INT1); also elsewhere on the board
/Top/MCU - Main FC/IMU2_SPI4_CLK: U402.13 (AP_SCL/AP_SCLK); also elsewhere on the board
/Top/MCU - Main FC/IMU2_SPI4_CS: U402.12 (AP_CS); also elsewhere on the board
/Top/MCU - Main FC/IMU2_SPI4_SDI: U402.14 (AP_SDA/AP_SDIO/AP_SDI); also elsewhere on the board
/Top/MCU - Main FC/IMU2_SPI4_SDO: U402.1 (AP_SDO/AP_AD0); also elsewhere on the board
GND: C401.2, C402.2, C403.2, C404.2, U401.6 (GND), U402.6 (GND); also elsewhere on the board

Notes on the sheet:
[${#}] ${COMMENT1}

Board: 4 copper layers, 268 parts (35 on the bottom side), 174 nets, no tracks yet.
